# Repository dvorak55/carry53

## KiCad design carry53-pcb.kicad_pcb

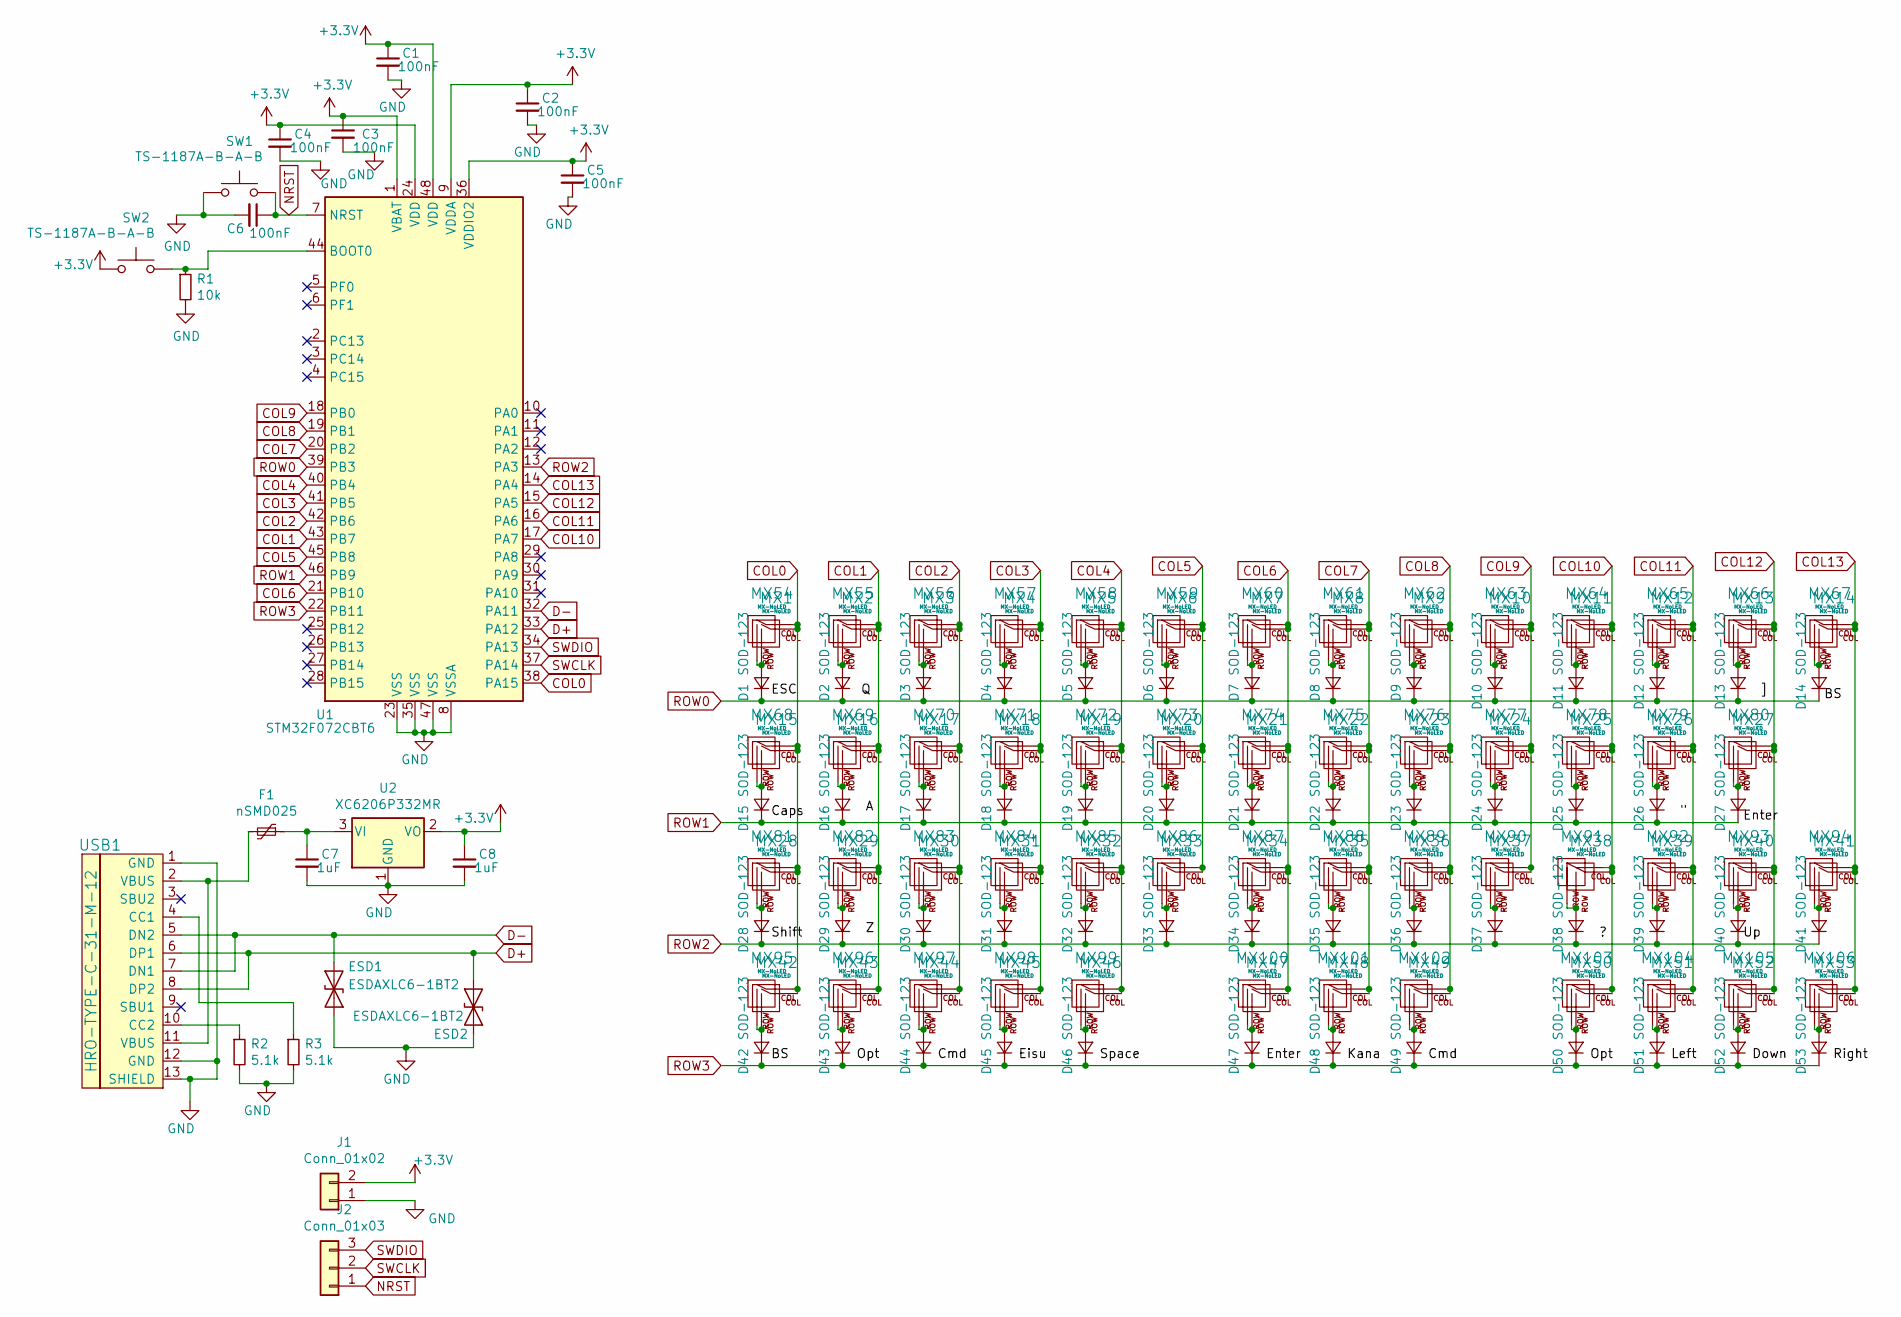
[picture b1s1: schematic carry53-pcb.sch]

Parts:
C1, C2, C3, C4, C5, C6: 100nF; C_0402_1005Metric
C7, C8: 1uF; C_0603_1608Metric
D1, D2, D3, D4, D5, D6, D7, D8, D9, D10, D11, D12, D13, D14, D15, D16, D17, D18, D19, D20, D21, D22, D23, D24, D25, D26, D27, D28, D29, D30, D31, D32, D33, D34, D35, D36, D37, D38, D39, D40, D41, D42, D43, D44, D45, D46, D47, D48, D49, D50, D51, D52, D53: SOD-123; D_SOD-123
ESD1, ESD2: ESDAXLC6-1BT2; D_0402_1005Metric
F1: nSMD025; Fuse_1206_3216Metric
J1: Conn_01x02; PinHeader_1x02_P2.54mm_Vertical
J2: Conn_01x03; PinHeader_1x03_P2.54mm_Vertical
MX1, MX14, MX45, MX46, MX47: MX-NoLED; MXOnly-1.5U-NoLED
MX2, MX3, MX4, MX5, MX6, MX7, MX8, MX9, MX10, MX11, MX12, MX13, MX16, MX17, MX18, MX19, MX20, MX21, MX22, MX23, MX24, MX25, MX26, MX29, MX30, MX31, MX32, MX33, MX34, MX35, MX36, MX37, MX38, MX39, MX40, MX41, MX51, MX52, MX53: MX-NoLED; MXOnly-1U-NoLED
MX15: MX-NoLED; MXOnly-1.75U-NoLED
MX27: MX-NoLED; MXOnly-2.25U-NoLED
MX28: MX-NoLED; MXOnly-2U-NoLED
MX42, MX43, MX44, MX48, MX49, MX50: MX-NoLED; MXOnly-1.25U-NoLED
MX54, MX55, MX56, MX57, MX58, MX59, MX60, MX61, MX62, MX63, MX64, MX65, MX66, MX67, MX68, MX69, MX70, MX71, MX72, MX73, MX74, MX75, MX76, MX77, MX78, MX79, MX80, MX81, MX82, MX83, MX84, MX85, MX86, MX87, MX88, MX89, MX90, MX91, MX92, MX93, MX94, MX95, MX96, MX97, MX98, MX99, MX100, MX101, MX102, MX103, MX104, MX105, MX106: MX-NoLED; KailhChoc-1U
R1: 10k; R_0603_1608Metric
R2, R3: 5.1k; R_0603_1608Metric
SW1, SW2: TS-1187A-B-A-B; SKQGADE010
U1: STM32F072CBT6; LQFP-48_7x7mm_P0.5mm
U2: XC6206P332MR; TSOT-23
USB1: HRO-TYPE-C-31-M-12; HRO-TYPE-C-31-M-12-HandSoldering

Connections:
+3V3: C1.1, C2.1, C3.1, C4.1, C5.1, C8.1, J1.2, SW2.1, U1.1 (VBAT), U1.9 (VDDA), U1.24 (VDD), U1.36 (VDDIO2), U1.48 (VDD), U2.2 (VO)
COL0: MX1.1 (COL), MX15.1 (COL), MX28.1 (COL), MX42.1 (COL), MX54.1 (COL), MX68.1 (COL), MX81.1 (COL), MX95.1 (COL), U1.38 (PA15)
COL1: MX2.1 (COL), MX16.1 (COL), MX29.1 (COL), MX43.1 (COL), MX55.1 (COL), MX69.1 (COL), MX82.1 (COL), MX96.1 (COL), U1.43 (PB7)
COL2: MX3.1 (COL), MX17.1 (COL), MX30.1 (COL), MX44.1 (COL), MX56.1 (COL), MX70.1 (COL), MX83.1 (COL), MX97.1 (COL), U1.42 (PB6)
COL3: MX4.1 (COL), MX18.1 (COL), MX31.1 (COL), MX45.1 (COL), MX57.1 (COL), MX71.1 (COL), MX84.1 (COL), MX98.1 (COL), U1.41 (PB5)
COL4: MX5.1 (COL), MX19.1 (COL), MX32.1 (COL), MX46.1 (COL), MX58.1 (COL), MX72.1 (COL), MX85.1 (COL), MX99.1 (COL), U1.40 (PB4)
COL5: MX6.1 (COL), MX20.1 (COL), MX33.1 (COL), MX59.1 (COL), MX73.1 (COL), MX86.1 (COL), U1.45 (PB8)
COL6: MX7.1 (COL), MX21.1 (COL), MX34.1 (COL), MX47.1 (COL), MX60.1 (COL), MX74.1 (COL), MX87.1 (COL), MX100.1 (COL), U1.21 (PB10)
COL7: MX8.1 (COL), MX22.1 (COL), MX35.1 (COL), MX48.1 (COL), MX61.1 (COL), MX75.1 (COL), MX88.1 (COL), MX101.1 (COL), U1.20 (PB2)
COL8: MX9.1 (COL), MX23.1 (COL), MX36.1 (COL), MX49.1 (COL), MX62.1 (COL), MX76.1 (COL), MX89.1 (COL), MX102.1 (COL), U1.19 (PB1)
COL9: MX10.1 (COL), MX24.1 (COL), MX37.1 (COL), MX63.1 (COL), MX77.1 (COL), MX90.1 (COL), U1.18 (PB0)
COL10: MX11.1 (COL), MX25.1 (COL), MX38.1 (COL), MX50.1 (COL), MX64.1 (COL), MX78.1 (COL), MX91.1 (COL), MX103.1 (COL), U1.17 (PA7)
COL11: MX12.1 (COL), MX26.1 (COL), MX39.1 (COL), MX51.1 (COL), MX65.1 (COL), MX79.1 (COL), MX92.1 (COL), MX104.1 (COL), U1.16 (PA6)
COL12: MX13.1 (COL), MX27.1 (COL), MX40.1 (COL), MX52.1 (COL), MX66.1 (COL), MX80.1 (COL), MX93.1 (COL), MX105.1 (COL), U1.15 (PA5)
COL13: MX14.1 (COL), MX41.1 (COL), MX53.1 (COL), MX67.1 (COL), MX94.1 (COL), MX106.1 (COL), U1.14 (PA4)
D+: ESD2.1 (A1), U1.33 (PA12), USB1.6 (DP1), USB1.8 (DP2)
D-: ESD1.1 (A1), U1.32 (PA11), USB1.5 (DN2), USB1.7 (DN1)
GND: C1.2, C2.2, C3.2, C4.2, C5.2, C6.2, C7.2, C8.2, ESD1.2 (A2), ESD2.2 (A2), J1.1, R1.2, R2.2, R3.2, SW1.1, U1.8 (VSSA), U1.23 (VSS), U1.35 (VSS), U1.47 (VSS), U2.1 (GND), USB1.1 (GND), USB1.12 (GND), USB1.13 (SHIELD)
NRST: C6.1, J2.1, SW1.2, U1.7 (NRST)
unnamed: C7.1, F1.1, U2.3 (VI)
unnamed: D1.2 (A), MX1.2 (ROW), MX54.2 (ROW)
unnamed: D2.2 (A), MX2.2 (ROW), MX55.2 (ROW)
unnamed: D3.2 (A), MX3.2 (ROW), MX56.2 (ROW)
unnamed: D4.2 (A), MX4.2 (ROW), MX57.2 (ROW)
unnamed: D5.2 (A), MX5.2 (ROW), MX58.2 (ROW)
unnamed: D6.2 (A), MX6.2 (ROW), MX59.2 (ROW)
unnamed: D7.2 (A), MX7.2 (ROW), MX60.2 (ROW)
unnamed: D8.2 (A), MX8.2 (ROW), MX61.2 (ROW)
unnamed: D9.2 (A), MX9.2 (ROW), MX62.2 (ROW)
unnamed: D10.2 (A), MX10.2 (ROW), MX63.2 (ROW)
unnamed: D11.2 (A), MX11.2 (ROW), MX64.2 (ROW)
unnamed: D12.2 (A), MX12.2 (ROW), MX65.2 (ROW)
unnamed: D13.2 (A), MX13.2 (ROW), MX66.2 (ROW)
unnamed: D14.2 (A), MX14.2 (ROW), MX67.2 (ROW)
unnamed: D15.2 (A), MX15.2 (ROW), MX68.2 (ROW)
unnamed: D16.2 (A), MX16.2 (ROW), MX69.2 (ROW)
unnamed: D17.2 (A), MX17.2 (ROW), MX70.2 (ROW)
unnamed: D18.2 (A), MX18.2 (ROW), MX71.2 (ROW)
unnamed: D19.2 (A), MX19.2 (ROW), MX72.2 (ROW)
unnamed: D20.2 (A), MX20.2 (ROW), MX73.2 (ROW)
unnamed: D21.2 (A), MX21.2 (ROW), MX74.2 (ROW)
unnamed: D22.2 (A), MX22.2 (ROW), MX75.2 (ROW)
unnamed: D23.2 (A), MX23.2 (ROW), MX76.2 (ROW)
unnamed: D24.2 (A), MX24.2 (ROW), MX77.2 (ROW)
unnamed: D25.2 (A), MX25.2 (ROW), MX78.2 (ROW)
unnamed: D26.2 (A), MX26.2 (ROW), MX79.2 (ROW)
unnamed: D27.2 (A), MX27.2 (ROW), MX80.2 (ROW)
unnamed: D28.2 (A), MX28.2 (ROW), MX81.2 (ROW)
unnamed: D29.2 (A), MX29.2 (ROW), MX82.2 (ROW)
unnamed: D30.2 (A), MX30.2 (ROW), MX83.2 (ROW)
unnamed: D31.2 (A), MX31.2 (ROW), MX84.2 (ROW)
unnamed: D32.2 (A), MX32.2 (ROW), MX85.2 (ROW)
unnamed: D33.2 (A), MX33.2 (ROW), MX86.2 (ROW)
unnamed: D34.2 (A), MX34.2 (ROW), MX87.2 (ROW)
unnamed: D35.2 (A), MX35.2 (ROW), MX88.2 (ROW)
unnamed: D36.2 (A), MX36.2 (ROW), MX89.2 (ROW)
unnamed: D37.2 (A), MX37.2 (ROW), MX90.2 (ROW)
unnamed: D38.2 (A), MX38.2 (ROW), MX91.2 (ROW)
unnamed: D39.2 (A), MX39.2 (ROW), MX92.2 (ROW)
unnamed: D40.2 (A), MX40.2 (ROW), MX93.2 (ROW)
unnamed: D41.2 (A), MX41.2 (ROW), MX94.2 (ROW)
unnamed: D42.2 (A), MX42.2 (ROW), MX95.2 (ROW)
unnamed: D43.2 (A), MX43.2 (ROW), MX96.2 (ROW)
unnamed: D44.2 (A), MX44.2 (ROW), MX97.2 (ROW)
unnamed: D45.2 (A), MX45.2 (ROW), MX98.2 (ROW)
unnamed: D46.2 (A), MX46.2 (ROW), MX99.2 (ROW)
unnamed: D47.2 (A), MX47.2 (ROW), MX100.2 (ROW)
unnamed: D48.2 (A), MX48.2 (ROW), MX101.2 (ROW)
unnamed: D49.2 (A), MX49.2 (ROW), MX102.2 (ROW)
unnamed: D50.2 (A), MX50.2 (ROW), MX103.2 (ROW)
unnamed: D51.2 (A), MX51.2 (ROW), MX104.2 (ROW)
unnamed: D52.2 (A), MX52.2 (ROW), MX105.2 (ROW)
unnamed: D53.2 (A), MX53.2 (ROW), MX106.2 (ROW)
unnamed: F1.2, USB1.2 (VBUS), USB1.11 (VBUS)
unnamed: R1.1, SW2.2, U1.44 (BOOT0)
unnamed: R2.1, USB1.10 (CC2)
unnamed: R3.1, USB1.4 (CC1)
ROW0: D1.1 (K), D2.1 (K), D3.1 (K), D4.1 (K), D5.1 (K), D6.1 (K), D7.1 (K), D8.1 (K), D9.1 (K), D10.1 (K), D11.1 (K), D12.1 (K), D13.1 (K), D14.1 (K), U1.39 (PB3)
ROW1: D15.1 (K), D16.1 (K), D17.1 (K), D18.1 (K), D19.1 (K), D20.1 (K), D21.1 (K), D22.1 (K), D23.1 (K), D24.1 (K), D25.1 (K), D26.1 (K), D27.1 (K), U1.46 (PB9)
ROW2: D28.1 (K), D29.1 (K), D30.1 (K), D31.1 (K), D32.1 (K), D33.1 (K), D34.1 (K), D35.1 (K), D36.1 (K), D37.1 (K), D38.1 (K), D39.1 (K), D40.1 (K), D41.1 (K), U1.13 (PA3)
ROW3: D42.1 (K), D43.1 (K), D44.1 (K), D45.1 (K), D46.1 (K), D47.1 (K), D48.1 (K), D49.1 (K), D50.1 (K), D51.1 (K), D52.1 (K), D53.1 (K), U1.22 (PB11)
SWCLK: J2.2, U1.37 (PA14)
SWDIO: J2.3, U1.34 (PA13)

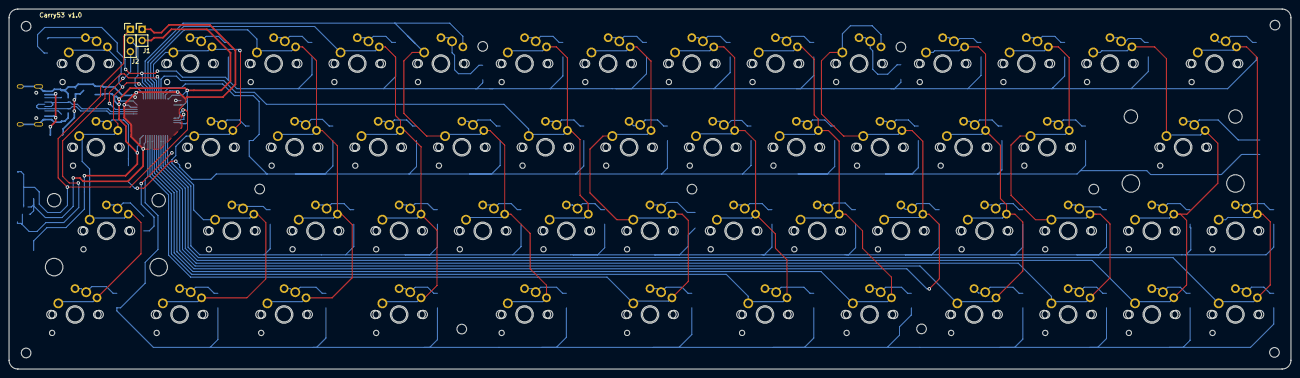
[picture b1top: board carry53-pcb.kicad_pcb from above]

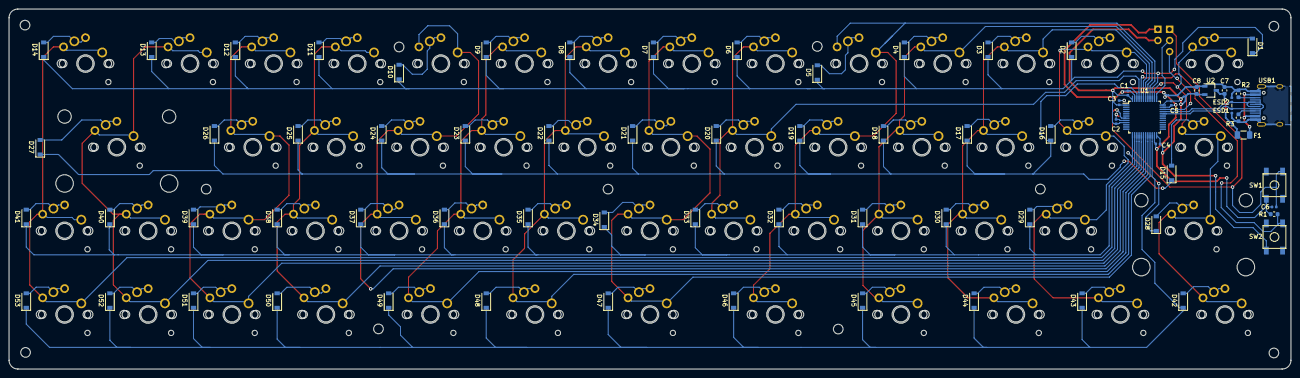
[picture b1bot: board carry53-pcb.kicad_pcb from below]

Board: 2 copper layers, 292.0 x 82.0 mm, 180 parts (72 on the bottom side), 83 nets.

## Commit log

2024-01-21 create kicad project
2024-01-21 Add submodules
2024-01-21 Add usb-c submodules
2024-01-21 add footprint
2024-01-26 sch susumeta
2024-02-21 haisen_hobo_dekita
2024-02-25 hobo kansei minaoshi hituyou kana
2024-02-26 kansei de iiyone
2024-02-26 garbar tukutta
2024-03-13 firmware test
    I made vial firmware for test.
2024-03-17 vial firmware almost done
2024-03-17 vial firmware almost done. 2
